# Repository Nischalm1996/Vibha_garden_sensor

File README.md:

# Vibha_garden_sensor

## GARDEN STATION
| NAME     | Pin |
|----------|-----|
| SDA      | A4  |
| SCL      | A5  |
| SOIL     | A7  |
| OK       | D5  |
| LEFT     | D4  |
| RIGHT    | D7  |
| BACK     | D6  |
| SOUND    | A3  |
| DHT11    | D2  |
| TX       | D0  |
| RX       | D1  |

### MODULES USED
- SOUND (LM393)
- DHT11
- MPU6050 GYROSCOPE
- SOIL MOISTURE
- ESP8266 NODEMCU
- ARDUINO NANO
- NAVIGATION MODULE
- DISPLAY I2C 16*2

###THINGS SPEAK DETAILS
####GMAIL DETAILS
ID- portableevironment@gmail.com
Password- EnvironmentPort@1
https://thingspeak.com/channels/1418539/private_show

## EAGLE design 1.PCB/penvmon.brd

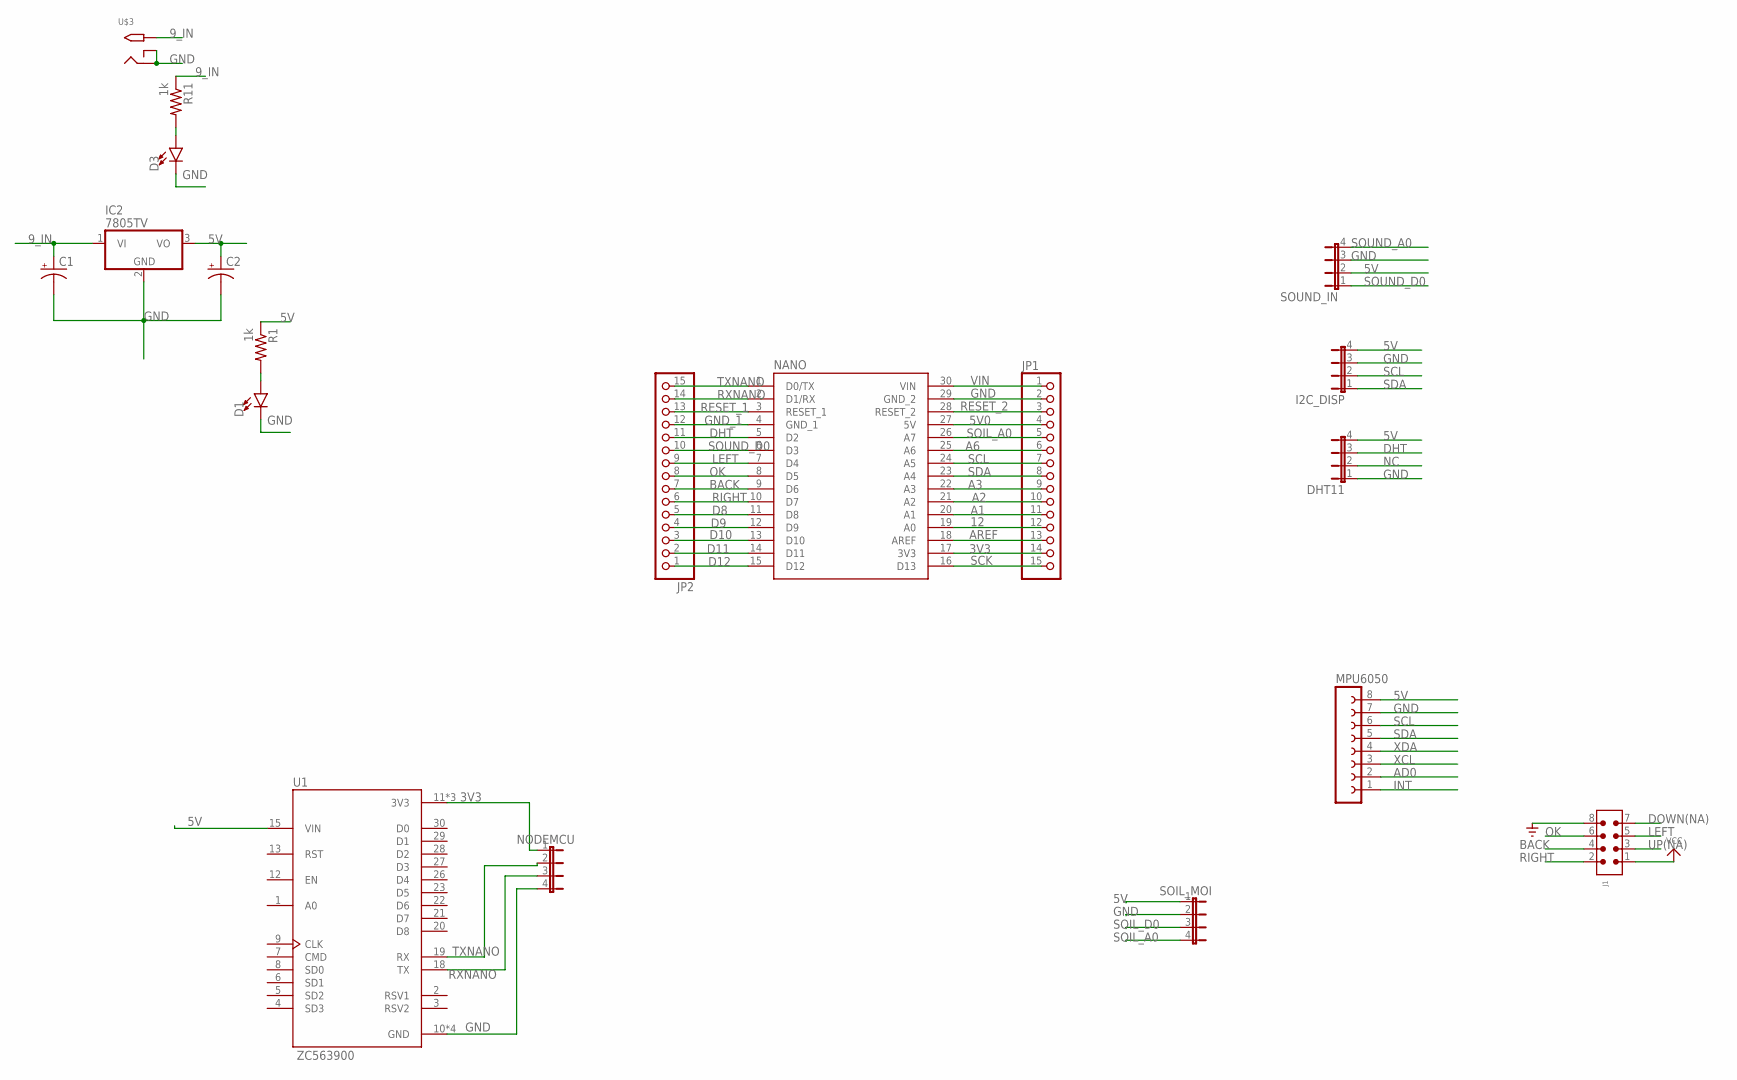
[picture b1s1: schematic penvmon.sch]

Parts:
C1, C2: CPOL-USE3.5-8; E3,5-8
D1, D3: LED3MM; LED_3MM
DHT11: JP4E; JP4
I2C_DISP: JP4E; JP4
IC2: 7805TV; TO220V
J1: 6120XX21621_61200821621; 61200821621
JP1, JP2: PINHD-1X15; 1X15
MPU6050: FE08-1; FE08
NANO: A000005; MODULE_A000005
NODEMCU: JP4E; JP4
R1, R11: 1k; M0805
SOIL_MOI: JP4E; JP4
SOUND_IN: JP4E; JP4
U1: ZC563900; MODULE_ZC563900
U$3: 2.1MMJACKTHM; PJ-102A

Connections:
3V3: JP1.14, NANO.17 (3V3), NODEMCU.1, U1.11 (3V3), U1.16 (3V3), U1.25 (3V3)
5V: C2.+, DHT11.4, I2C_DISP.4, IC2.3 (VO), MPU6050.8, R1.1, SOIL_MOI.1, SOUND_IN.2, U1.15 (VIN)
5V0: JP1.4, NANO.27 (5V)
9_IN: C1.+, IC2.1 (VI), R11.1, U$3.TIP
12: JP1.12, NANO.19 (A0)
A1: JP1.11, NANO.20 (A1)
A2: JP1.10, NANO.21 (A2)
A3: JP1.9, NANO.22 (A3)
A6: JP1.6, NANO.25 (A6)
AD0: MPU6050.2
AREF: JP1.13, NANO.18 (AREF)
BACK: J1.4, JP2.7, NANO.9 (D6)
D8: JP2.5, NANO.11 (D8)
D9: JP2.4, NANO.12 (D9)
D10: JP2.3, NANO.13 (D10)
D11: JP2.2, NANO.14 (D11)
D12: JP2.1, NANO.15 (D12)
DHT: DHT11.3, JP2.11, NANO.5 (D2)
DOWN(NA): J1.7
GND: C1.-, C2.-, D1.K (C), D3.K (C), DHT11.1, I2C_DISP.3, IC2.2 (GND), J1.8, JP1.2, MPU6050.7, NANO.29 (GND_2), NODEMCU.4, SOIL_MOI.2, SOUND_IN.3, U1.10 (GND), U1.14 (GND), U1.17 (GND), U1.24 (GND), U$3.RING, U$3.RING_SW
GND_1: JP2.12, NANO.4 (GND_1)
INT: MPU6050.1
LEFT: J1.5, JP2.9, NANO.7 (D4)
unnamed: D3.A, R11.2
unnamed: D1.A, R1.2
NC: DHT11.2
OK: J1.6, JP2.8, NANO.8 (D5)
RESET_1: JP2.13, NANO.3 (RESET_1)
RESET_2: JP1.3, NANO.28 (RESET_2)
RIGHT: J1.2, JP2.6, NANO.10 (D7)
RXNANO: JP2.14, NANO.2 (D1/RX), NODEMCU.3, U1.18 (TX)
SCK: JP1.15, NANO.16 (D13)
SCL: I2C_DISP.2, JP1.7, MPU6050.6, NANO.24 (A5)
SDA: I2C_DISP.1, JP1.8, MPU6050.5, NANO.23 (A4)
SOIL_A0: JP1.5, NANO.26 (A7), SOIL_MOI.4
SOIL_D0: SOIL_MOI.3
SOUND_A0: SOUND_IN.4
SOUND_D0: JP2.10, NANO.6 (D3), SOUND_IN.1
TXNANO: JP2.15, NANO.1 (D0/TX), NODEMCU.2, U1.19 (RX)
UP(NA): J1.3
VCC: J1.1
VIN: JP1.1, NANO.30 (VIN)
XCL: MPU6050.3
XDA: MPU6050.4

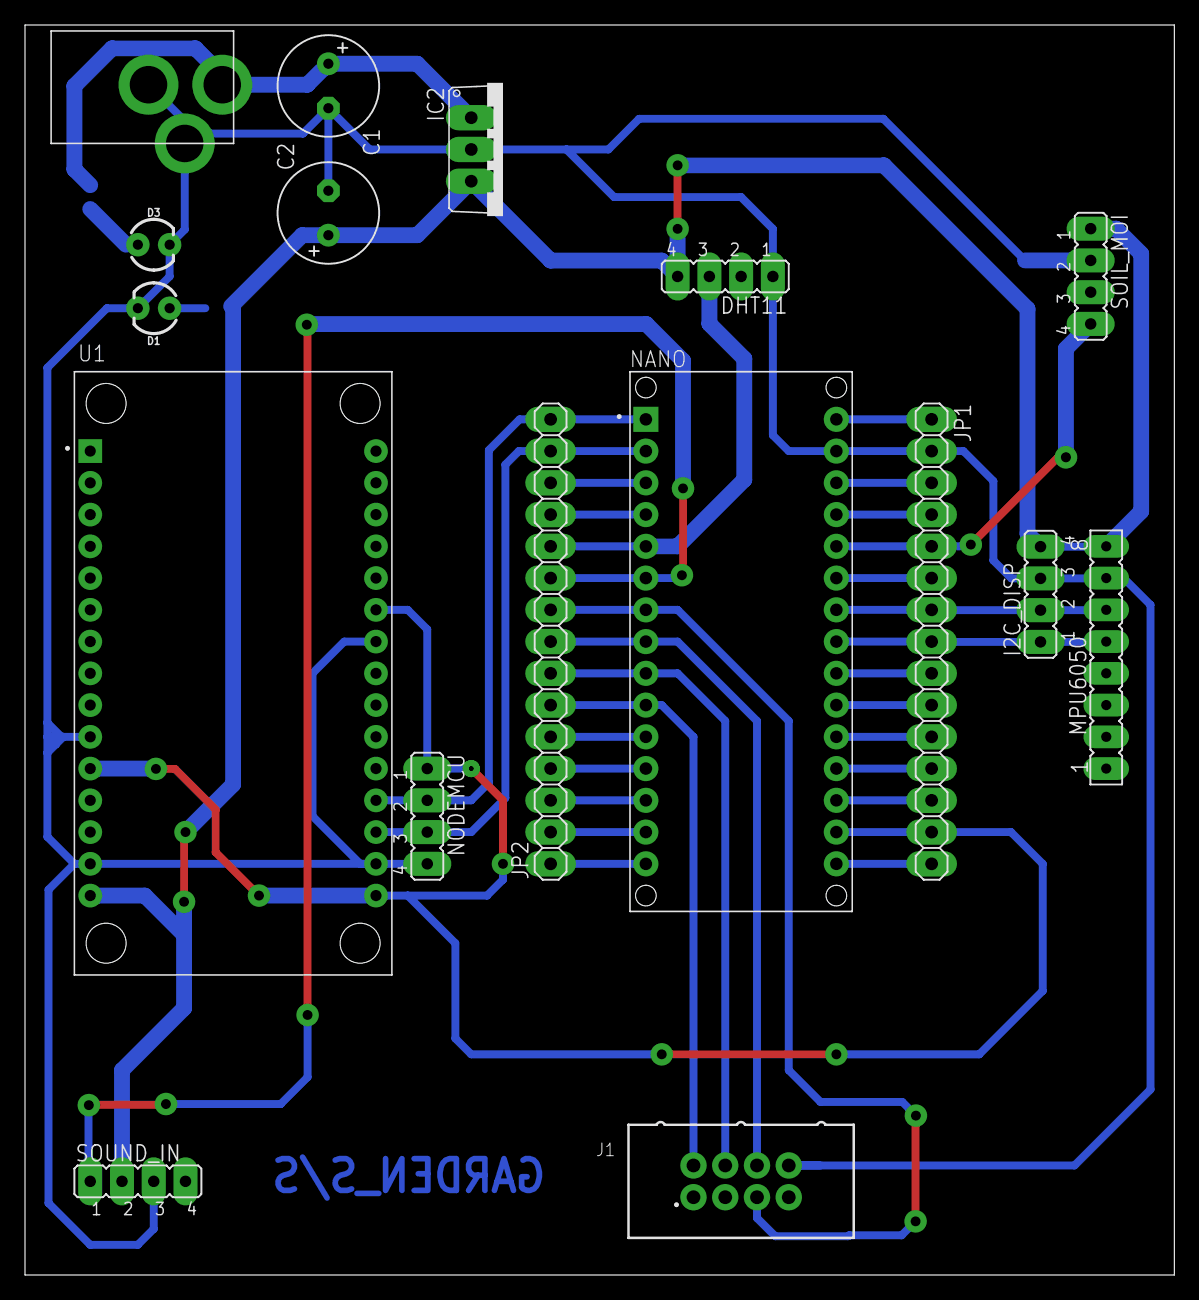
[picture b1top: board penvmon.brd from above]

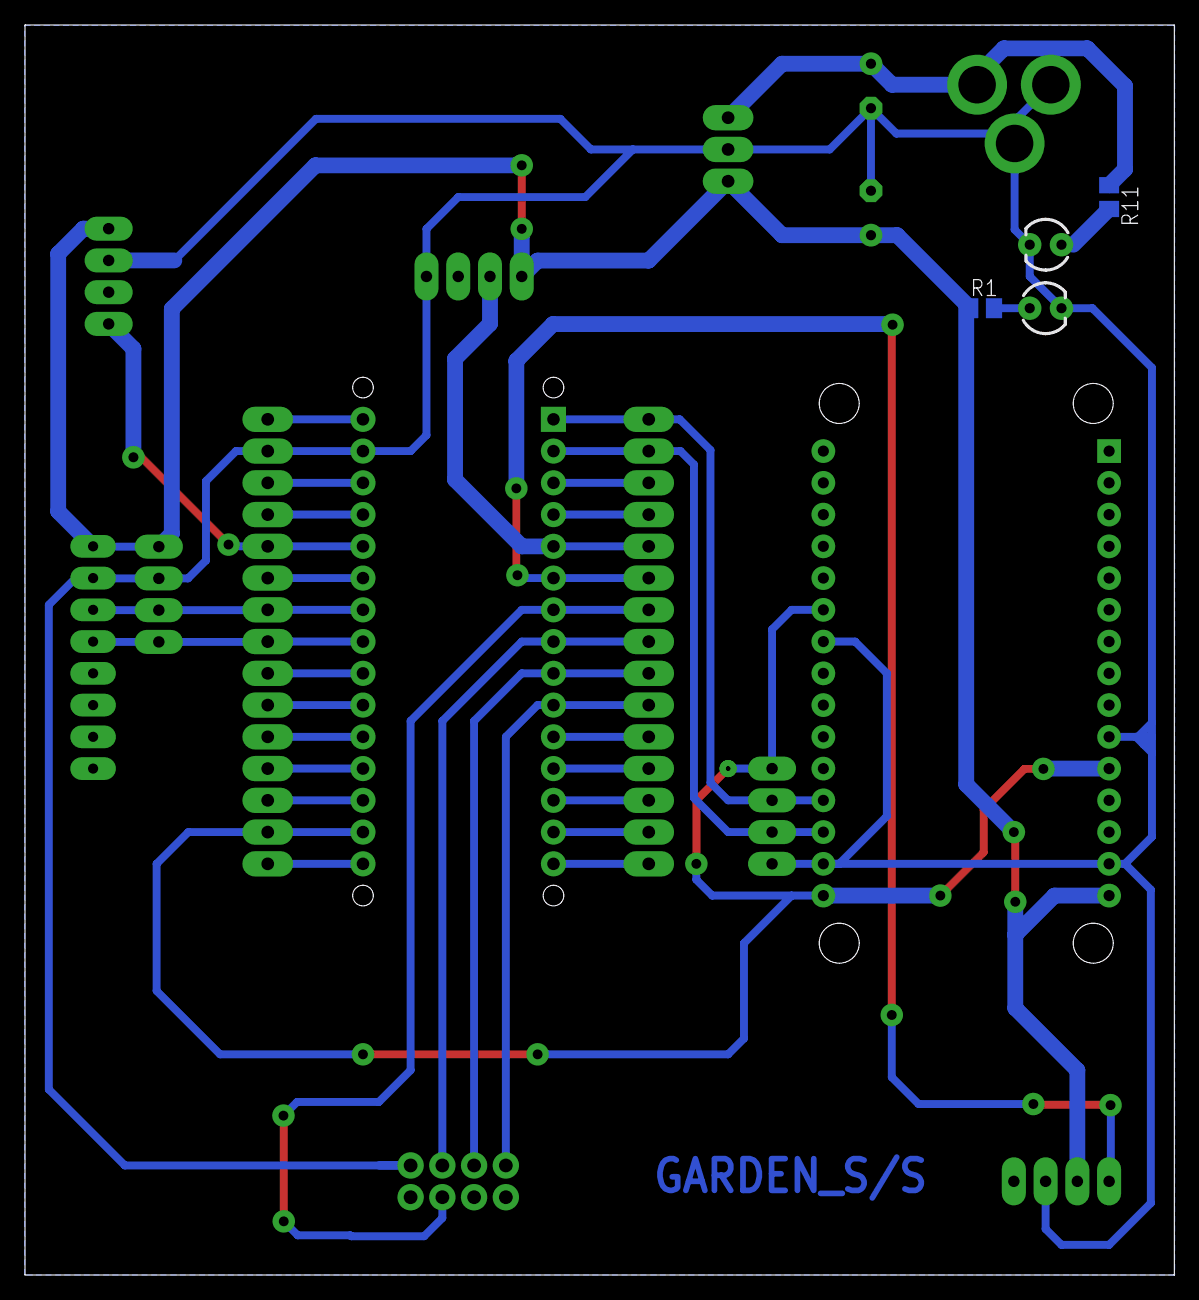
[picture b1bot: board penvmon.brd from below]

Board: 2 copper layers, 91.9 x 100.0 mm, 19 parts (2 on the bottom side), 34 nets.

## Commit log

2021-03-12 First push
    edited readme.md
2021-03-12 first pull
    edited readme
2021-03-12 changed Placement- routing and check needed
2021-03-13 vibha_layout_done
    kindly check the layout once
2021-03-13 just_a_little_correction_vibha_project
    all the sensors are added and designed
2021-03-14 made layout changes
2021-03-16 added pcb image
2021-03-16 changed directory structure
2021-03-16 updated image
2021-04-07 PINS_UPDATED
    All the assigned pins as per the design updated
2021-04-16 dht11 and soil sensor code
    sensor code created
2021-04-16 update platformini
2021-04-17 Create workspace.code-workspace
2021-05-01 test
2021-06-02 dht11 code added
2021-06-02 soil added
2021-06-07 working arduino v1
2021-06-08 ESP_Arduino added
2021-06-08 added the edited main program
2021-06-08 push repair
2021-06-08 repaired
2021-06-14 just corrected mpu sub function and compiledd
2021-06-17 arduino final v1
2021-06-17 nodemcu v1 working
2021-06-29 made noise sensor updates
2021-07-19 wifi issue solved

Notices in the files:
parts and their libraries:
SparkFun-LED: Licensing: Creative Commons ShareAlike 4.0 International - https://creativecommons.org/licenses/by-sa/4.0
Wurth_Connectors_WR-BHD: Copyright: Würth Elektronik
